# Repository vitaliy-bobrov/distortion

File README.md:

# Distortion

Modern take on '78 MIJ DS-1 by Boss schematic.

The repository contains KiCad source files: schematic, PCB, BOM.

## Schematic

## PCB (3D preview)

## Interactive BOM

👉 [BOM](https://vitaliy-bobrov.github.io/distortion/)

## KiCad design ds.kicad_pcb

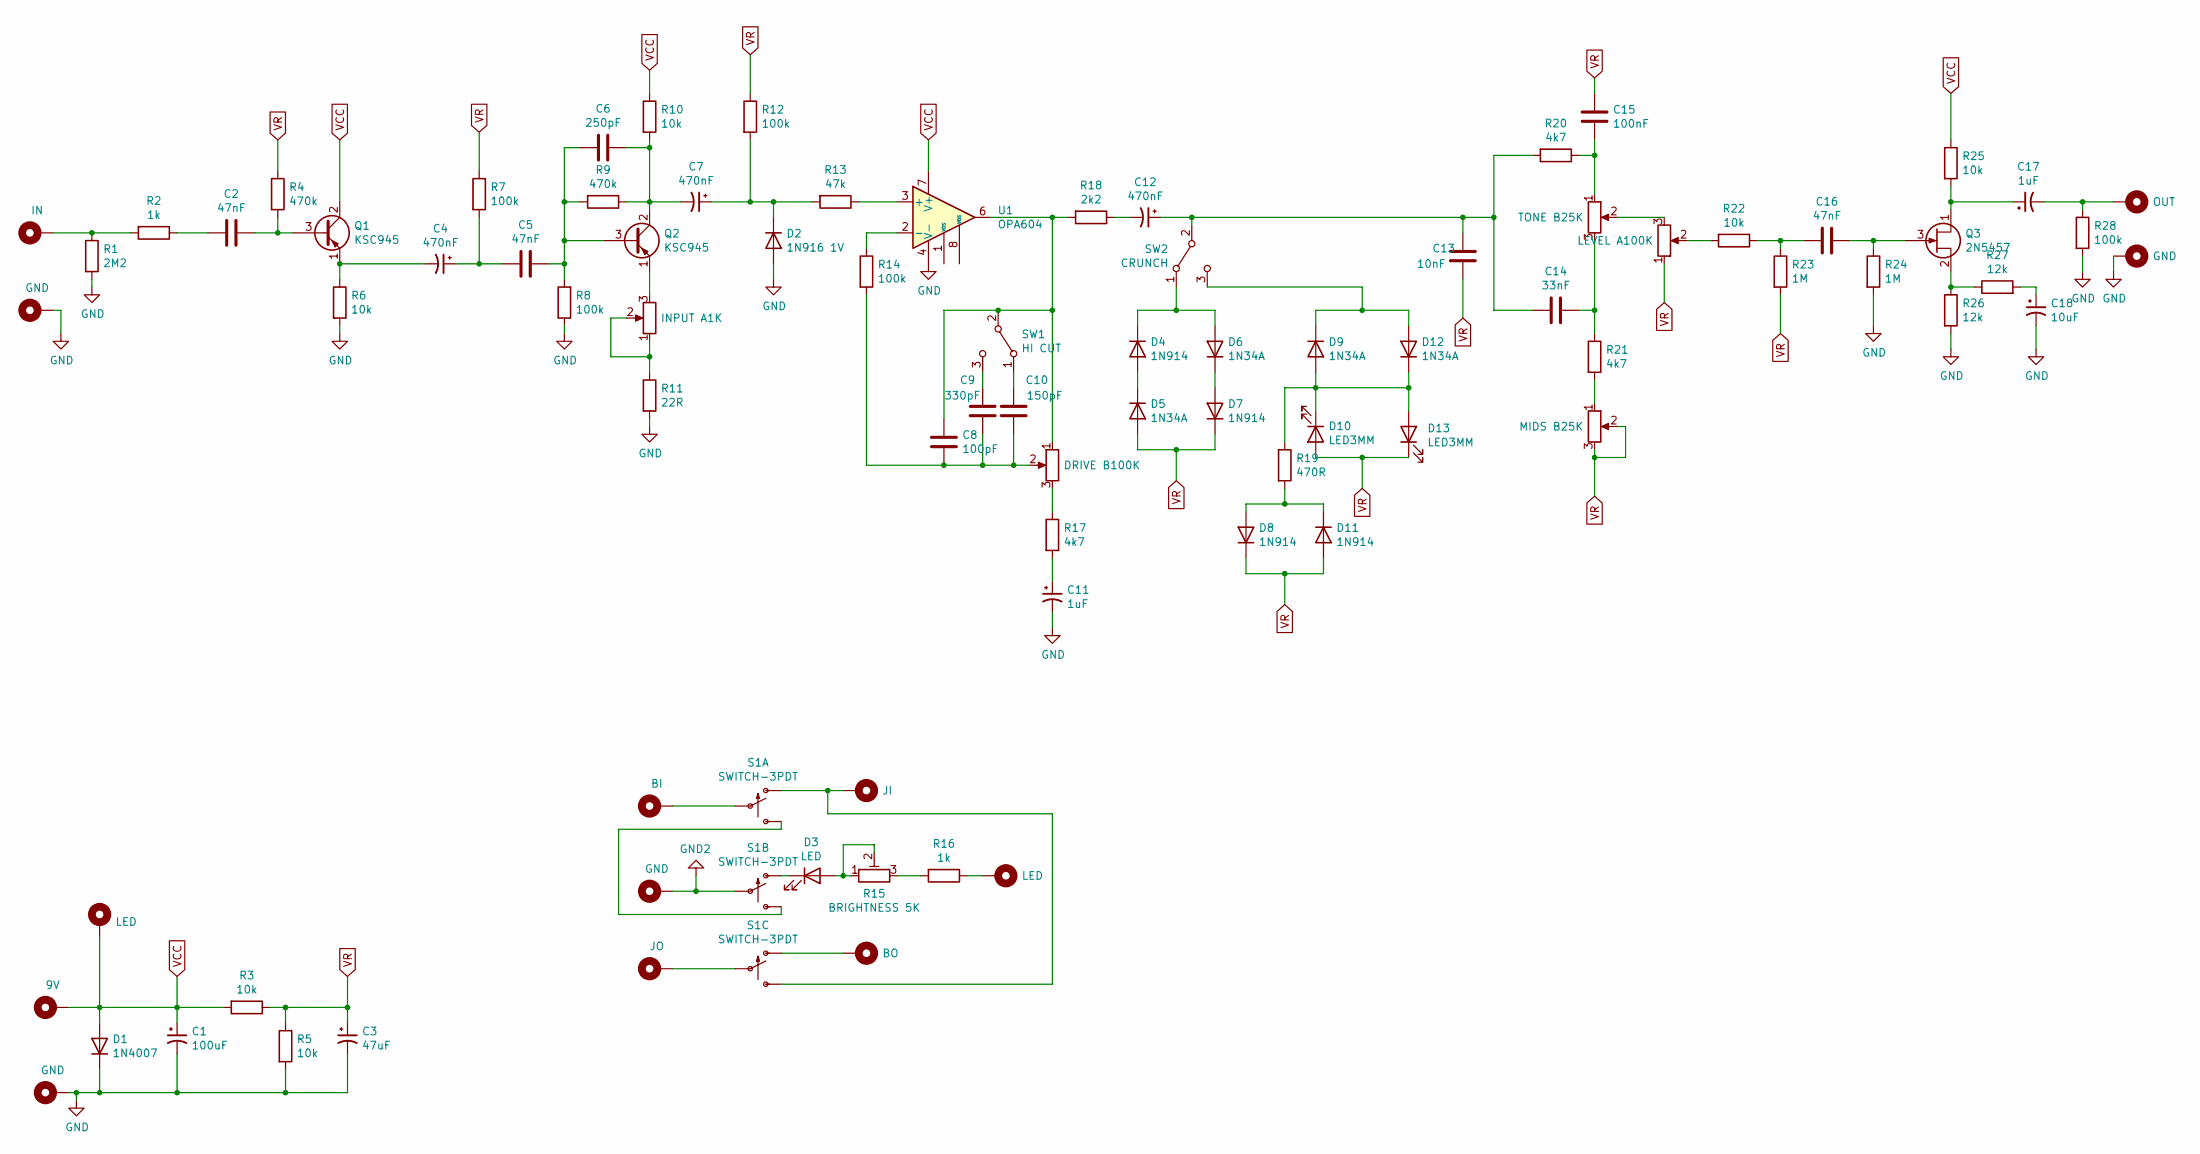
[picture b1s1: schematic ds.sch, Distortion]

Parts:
C1: 100uF; 0502
C2, C5, C16: 47nF; 0.2%22.SML
C3: 47uF; 0502
C4, C7, C12: 470nF; 0.2%22.SML
C6: 250pF; 0.2%22.MED
C8: 100pF; 0.2%22.MED
C9: 330pF; 0.2%22.MED
C10: 150pF; 0.2%22.MED
C11, C17: 1uF; 0502
C13: 10nF; 0.2%22.SML
C14: 33nF; 0.2%22.SML
C15: 100nF; 0.2%22.SML
C18: 10uF; 0502
D1: 1N4007; DO41-2
D2: 1N916 1V; DO35-2
D3: LED; 3MM_IO
D4, D7, D8, D11: 1N914; DO35-2
D5, D6, D9, D12: 1N34A; DO35-2
D10, D13: LED3MM; 3MM_1
H1: IN; PAD1
H2, H4, H7, H13: GND; PAD1
H3: 9V; PAD1
H5, H11: LED; PAD1
H6: BI; PAD1
H8: JO; PAD1
H9: JI; PAD1
H10: BO; PAD1
H12: OUT; PAD1
Q1, Q2: KSC945; TO92
Q3: 2N5457; TO92
R1: 2M2; 0.3%22.B
R2, R16: 1k; 0.3%22.B
R3, R5, R6, R10, R22, R25: 10k; 0.3%22.B
R4, R9: 470k; 0.3%22.B
R7, R8, R12, R14, R28: 100k; 0.3%22.B
R11: 22R; 0.3%22.B
R13: 47k; 0.3%22.B
R15: BRIGHTNESS 5K; TRIM1
R17, R20, R21: 4k7; 0.3%22.B
R18: 2k2; 0.3%22.B
R19: 470R; 0.3%22.B
R23, R24: 1M; 0.3%22.B
R26, R27: 12k; 0.3%22.B
RV1: INPUT A1K; 9MM_METAL_SHAFT
RV2: DRIVE B100K; 9MM_METAL_SHAFT
RV3: TONE B25K; 9MM_METAL_SHAFT
RV4: MIDS B25K; 9MM_METAL_SHAFT
RV5: LEVEL A100K; 9MM_METAL_SHAFT
S1: SWITCH-3PDT; 3PDT.LUGS.SPF
SW1: HI CUT; SPDT.LUGS
SW2: CRUNCH; SPDT.LUGS
U1: OPA604; DIP08

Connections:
GND: C1.2, C3.2, C11.2, C18.2, D1.1 (K), D2.2 (A), H2.1, H4.1, H13.1, R1.2, R5.2, R6.2, R8.1, R11.2, R24.2, R26.2, R28.2, U1.4 (V-)
GND2: H7.1, S1.P$5
unnamed: C2.1, Q1.3 (B), R4.2
unnamed: C2.2, R2.1
unnamed: C4.1, C5.2, R7.2
unnamed: C4.2, Q1.1 (E), R6.1
unnamed: C5.1, C6.2, Q2.3 (B), R8.2, R9.2
unnamed: C6.1, C7.2, Q2.2 (C), R9.1, R10.2
unnamed: C7.1, D2.1 (K), R12.2, R13.2
unnamed: C8.2, R18.2, RV2.1, SW1.2 (B), U1.6
unnamed: C9.2, SW1.3 (C)
unnamed: C8.1, C9.1, C10.1, R14.2, RV2.2
unnamed: C10.2, SW1.1 (A)
unnamed: C11.1, R17.2
unnamed: C12.1, C13.1, C14.2, R20.2, SW2.2 (B)
unnamed: C12.2, R18.1
unnamed: C14.1, R21.1, RV3.3
unnamed: C15.2, R20.1, RV3.1
unnamed: C16.1, Q3.3 (G), R24.1
unnamed: C16.2, R22.1, R23.1
unnamed: C17.1, Q3.1 (D), R25.2
unnamed: C17.2, H12.1, R28.1
unnamed: C18.1, R27.2
unnamed: D3.1 (K), S1.P$4 (O)
unnamed: D3.2 (A), R15.1, R15.2
unnamed: D4.1 (K), D6.2 (A), SW2.1 (A)
unnamed: D4.2 (A), D5.1 (K)
unnamed: D6.1 (K), D7.2 (A)
unnamed: D9.2 (A), D10.1 (K), D12.1 (K), D13.2 (A), R19.1
unnamed: D8.2 (A), D11.1 (K), R19.2
unnamed: D9.1 (K), D12.2 (A), SW2.3 (C)
unnamed: H1.1, R1.1, R2.2
unnamed: H6.1, S1.P$2
unnamed: H8.1, S1.P$8
unnamed: H9.1, S1.P$1 (O), S1.P$9 (S)
unnamed: H10.1, S1.P$7 (O)
unnamed: H11.1, R16.1
unnamed: Q2.1 (E), RV1.3
unnamed: Q3.2 (S), R26.1, R27.1
unnamed: R11.1, RV1.1, RV1.2
unnamed: R13.1, U1.3 (+)
unnamed: R14.1, U1.2 (-)
unnamed: R15.3, R16.2
unnamed: R17.1, RV2.3
unnamed: R21.2, RV4.1
unnamed: R22.2, RV5.2
unnamed: RV3.2, RV5.3
unnamed: S1.P$3 (S), S1.P$6 (S)
VCC: C1.1, D1.2 (A), H3.1, H5.1, Q1.2 (C), R3.2, R10.1, R25.1, U1.7 (V+)
VR: C3.1, C13.2, C15.1, D5.2 (A), D7.1 (K), D8.1 (K), D10.2 (A), D11.2 (A), D13.1 (K), R3.1, R4.1, R5.1, R7.1, R12.1, R23.2, RV4.2, RV4.3, RV5.1

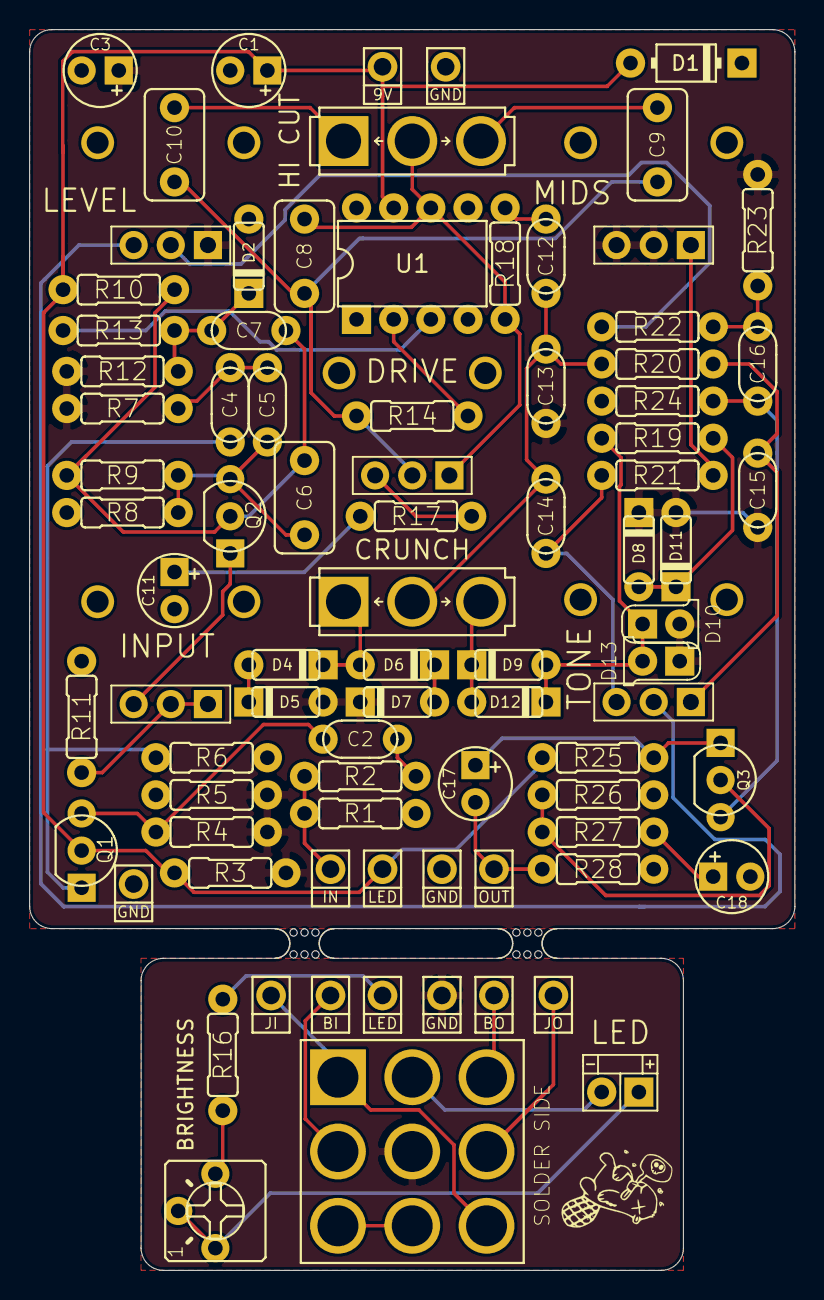
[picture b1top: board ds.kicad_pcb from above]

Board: 2 copper layers, 52.3 x 84.8 mm, 86 parts (0 on the bottom side), 50 nets.

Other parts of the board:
mouse-bite-2mm-slot, mouse-bite-2mm-slot#2: VAL**; mouse-bite-2mm-slot

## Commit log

2020-10-04 v1.1
2020-10-04 fix images path
